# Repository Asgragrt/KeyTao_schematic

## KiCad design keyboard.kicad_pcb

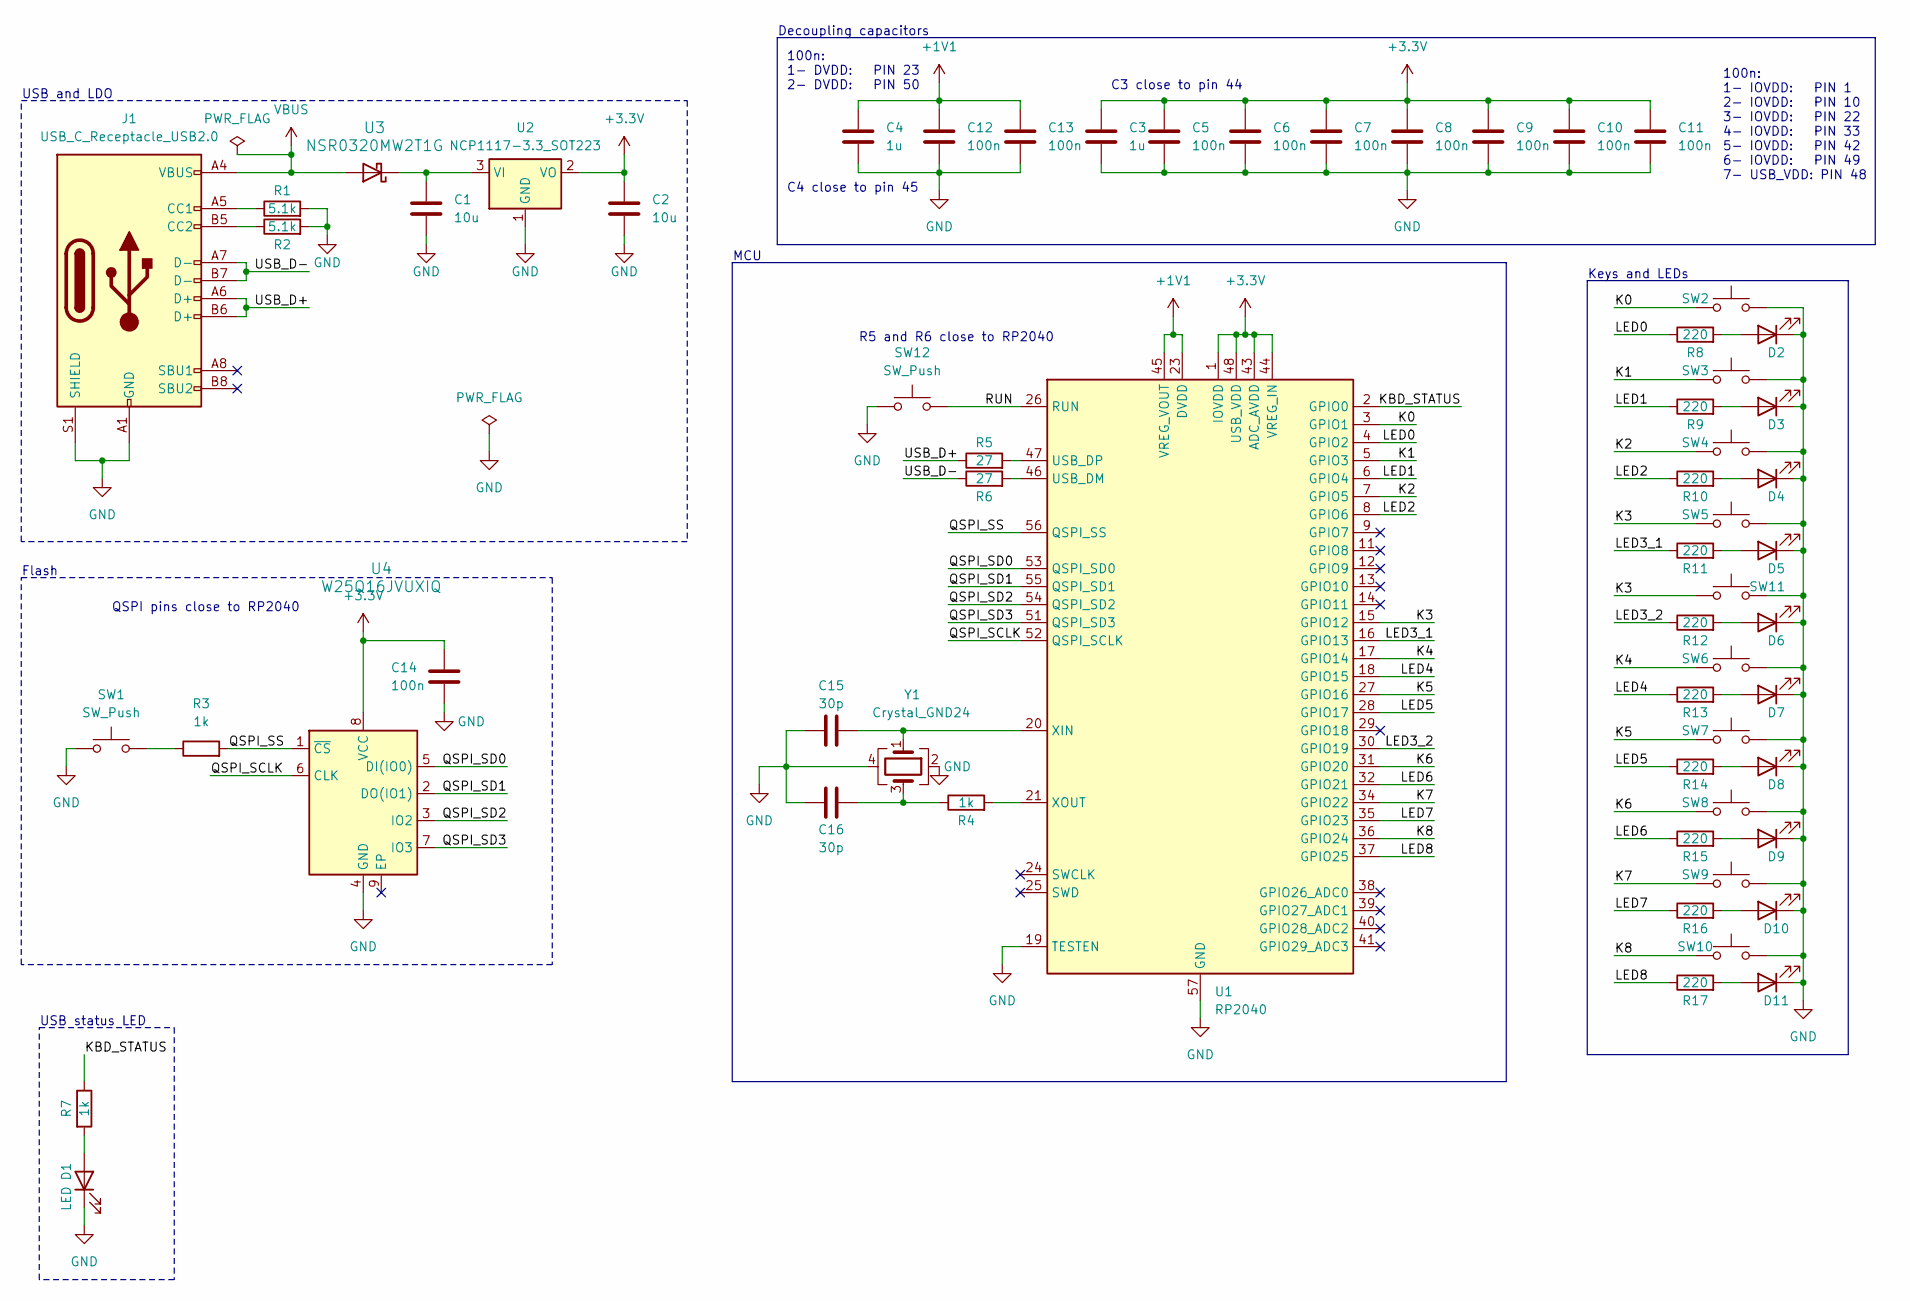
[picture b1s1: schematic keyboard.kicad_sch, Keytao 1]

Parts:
C1, C2: 10u; C_0402_1005Metric; JLCPCB Part# C15525
C3, C4: 1u; C_0402_1005Metric; JLCPCB Part# C52923
C5, C6, C7, C8, C9, C10, C11, C12, C13, C14: 100n; C_0402_1005Metric; JLCPCB Part# C1525
C15, C16: 30p; C_0402_1005Metric; JLCPCB Part# C1570
D1: LED; LED_0603_1608Metric; JLCPCB Part# C72038
D2, D3, D4, D5, D6, D7, D8, D9, D10, D11: LED; LED_0805_2012Metric; JLCPCB Part# C84256
J1: USB_C_Receptacle_USB2.0; USB_C_Receptacle_HRO_TYPE-C-31-M-12; JLCPCB Part# C165948
R1, R2: 5.1k; R_0805_2012Metric; JLCPCB Part# C27834
R3, R4, R7: 1k; R_0402_1005Metric; JLCPCB Part# C11702
R5, R6: 27; R_0603_1608Metric; JLCPCB Part# C25190
R8, R9, R10, R11, R12, R13, R14, R15, R16, R17: 220; R_0402_1005Metric; JLCPCB Part# C25091
SW1, SW12: SW_Push; SW_Push_1P1T_XKB_TS-1187A; JLCPCB Part# C318884
SW2, SW3, SW4, SW5, SW6, SW7, SW8, SW9, SW10, SW11: SW_Push; MXOnly-1U-Hotswap-Antishear_1; JLCPCB Part# C5156480
U1: RP2040; QFN-56-1EP_7x7mm_P0.4mm_EP3.2x3.2mm; JLCPCB Part# C2040
U2: NCP1117-3.3_SOT223; SOT-223-3_TabPin2; JLCPCB Part# C146799
U3: NSR0320MW2T1G; D_SOD-323; JLCPCB Part# C48192
U4: W25Q16JVUXIQ; W25Q16JVUXIQ_WIN; JLCPCB Part# C2843335
Y1: Crystal_GND24; Crystal_SMD_3225-4Pin_3.2x2.5mm; JLCPCB Part# C9002

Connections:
+1V1: C4.1, C12.1, C13.1, U1.23 (DVDD), U1.45 (VREG_VOUT), U1.50 (DVDD)
+3.3V: C2.1, C3.1, C5.1, C6.1, C7.1, C8.1, C9.1, C10.1, C11.1, C14.1, U1.1 (IOVDD), U1.10 (IOVDD), U1.22 (IOVDD), U1.33 (IOVDD), U1.42 (IOVDD), U1.43 (ADC_AVDD), U1.44 (VREG_IN), U1.48 (USB_VDD), U1.49 (IOVDD), U2.2 (VO), U4.8 (VCC)
/K0: SW2.2, U1.3 (GPIO1)
/K1: SW3.2, U1.5 (GPIO3)
/K2: SW4.2, U1.7 (GPIO5)
/K3: SW5.2, SW11.1, U1.15 (GPIO12)
/K4: SW6.2, U1.17 (GPIO14)
/K5: SW7.2, U1.27 (GPIO16)
/K6: SW8.2, U1.31 (GPIO20)
/K7: SW9.2, U1.34 (GPIO22)
/K8: SW10.2, U1.36 (GPIO24)
/KBD_STATUS: R7.1, U1.2 (GPIO0)
/LED0: R8.1, U1.4 (GPIO2)
/LED1: R9.1, U1.6 (GPIO4)
/LED2: R10.1, U1.8 (GPIO6)
/LED3_1: R11.1, U1.16 (GPIO13)
/LED3_2: R12.1, U1.30 (GPIO19)
/LED4: R13.1, U1.18 (GPIO15)
/LED5: R14.1, U1.28 (GPIO17)
/LED6: R15.1, U1.32 (GPIO21)
/LED7: R16.1, U1.35 (GPIO23)
/LED8: R17.1, U1.37 (GPIO25)
/QSPI_SCLK: U1.52 (QSPI_SCLK), U4.6 (CLK)
/QSPI_SD0: U1.53 (QSPI_SD0), U4.5 (DI(IO0))
/QSPI_SD1: U1.55 (QSPI_SD1), U4.2 (DO(IO1))
/QSPI_SD2: U1.54 (QSPI_SD2), U4.3 (IO2)
/QSPI_SD3: U1.51 (QSPI_SD3), U4.7 (IO3)
/QSPI_SS: R3.2, U1.56 (QSPI_SS), U4.1 (~CS)
/RUN: SW12.2, U1.26 (RUN)
/USB_D+: J1.A6 (D+), J1.B6 (D+), R5.1
/USB_D-: J1.A7 (D-), J1.B7 (D-), R6.1
GND: C1.2, C2.2, C3.2, C4.2, C5.2, C6.2, C7.2, C8.2, C9.2, C10.2, C11.2, C12.2, C13.2, C14.2, C15.1, C16.1, D1.1 (K), D2.1 (K), D3.1 (K), D4.1 (K), D5.1 (K), D6.1 (K), D7.1 (K), D8.1 (K), D9.1 (K), D10.1 (K), D11.1 (K), J1.A1 (GND), J1.A12 (GND), J1.B1 (GND), J1.B12 (GND), J1.S1 (SHIELD), R1.2, R2.2, SW1.1, SW2.1, SW3.1, SW4.1, SW5.1, SW6.1, SW7.1, SW8.1, SW9.1, SW10.1, SW11.2, SW12.1, U1.19 (TESTEN), U1.57 (GND), U2.1 (GND), U4.4 (GND), Y1.2, Y1.4
unnamed: C16.2, R4.1, Y1.3
unnamed: D1.2 (A), R7.2
unnamed: D2.2 (A), R8.2
unnamed: D3.2 (A), R9.2
unnamed: D4.2 (A), R10.2
unnamed: D5.2 (A), R11.2
unnamed: D6.2 (A), R12.2
unnamed: D7.2 (A), R13.2
unnamed: D8.2 (A), R14.2
unnamed: D9.2 (A), R15.2
unnamed: D10.2 (A), R16.2
unnamed: D11.2 (A), R17.2
unnamed: J1.A5 (CC1), R1.1
unnamed: J1.B5 (CC2), R2.1
unnamed: R3.1, SW1.2
unnamed: R6.2, U1.46 (USB_DM)
unnamed: R5.2, U1.47 (USB_DP)
unnamed: C15.2, U1.20 (XIN), Y1.1
unnamed: R4.2, U1.21 (XOUT)
unnamed: C1.1, U2.3 (VI), U3.1 (K)
VBUS: J1.A4 (VBUS), J1.A9 (VBUS), J1.B4 (VBUS), J1.B9 (VBUS), U3.2 (A)

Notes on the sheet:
C4 close to pin 45
100n: 1- IOVDD: PIN 1 2- IOVDD: PIN 10 3- IOVDD: PIN 22 4- IOVDD: PIN 33 5- IOVDD: PIN 42 6- IOVDD: PIN 49 7- USB_VDD: PIN 48
Keys and LEDs
MCU
Flash
QSPI pins close to RP2040
C3 close to pin 44
USB and LDO
USB status LED
100n: 1- DVDD: PIN 23 2- DVDD: PIN 50
R5 and R6 close to RP2040
Decoupling capacitors

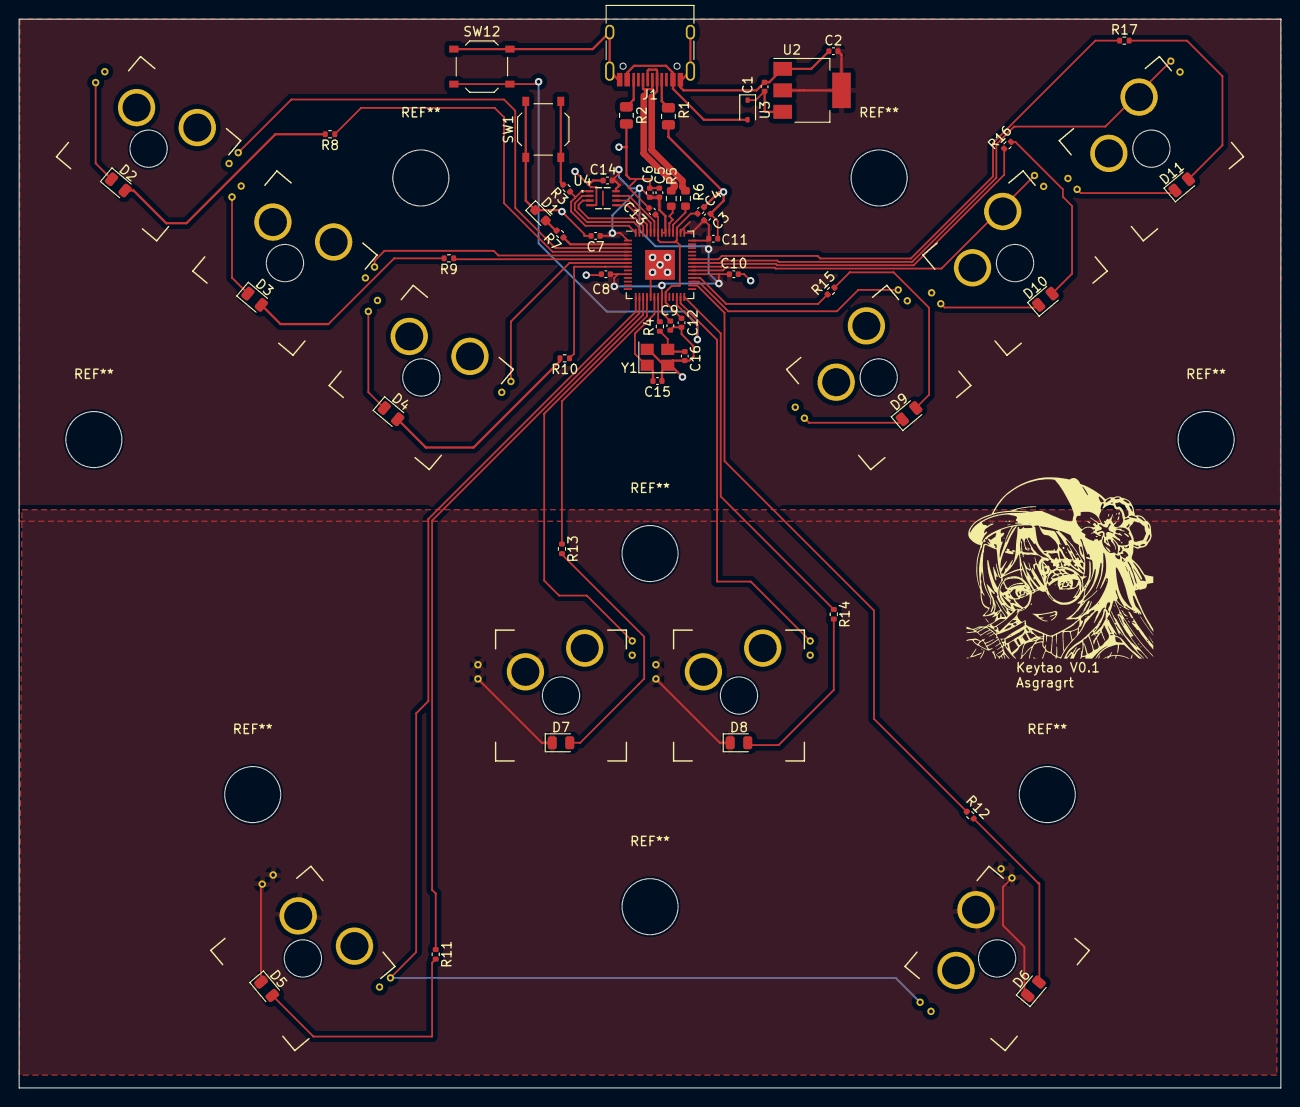
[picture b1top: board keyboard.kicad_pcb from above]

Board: 2 copper layers, 135.0 x 114.4 mm, 62 parts (0 on the bottom side), 53 nets.

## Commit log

2023-07-21 Added PCB files
2023-07-21 Keyboard-backups ignore
